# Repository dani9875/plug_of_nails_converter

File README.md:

# Plug of nails converter

# How to
Coming soon...

## Release notes

### Version: v3.0
Changelog:
- USB and free-lead power input  
- J-Link EDU Mini support header

### Version: v2.0
Changelog:
- Component library added as submodule
- KiBot config first usable file finished
. Connectors changed sides

### Version: v1.0
Changelog:
- Initial 2.54 mm and IDC 2x5 header connection

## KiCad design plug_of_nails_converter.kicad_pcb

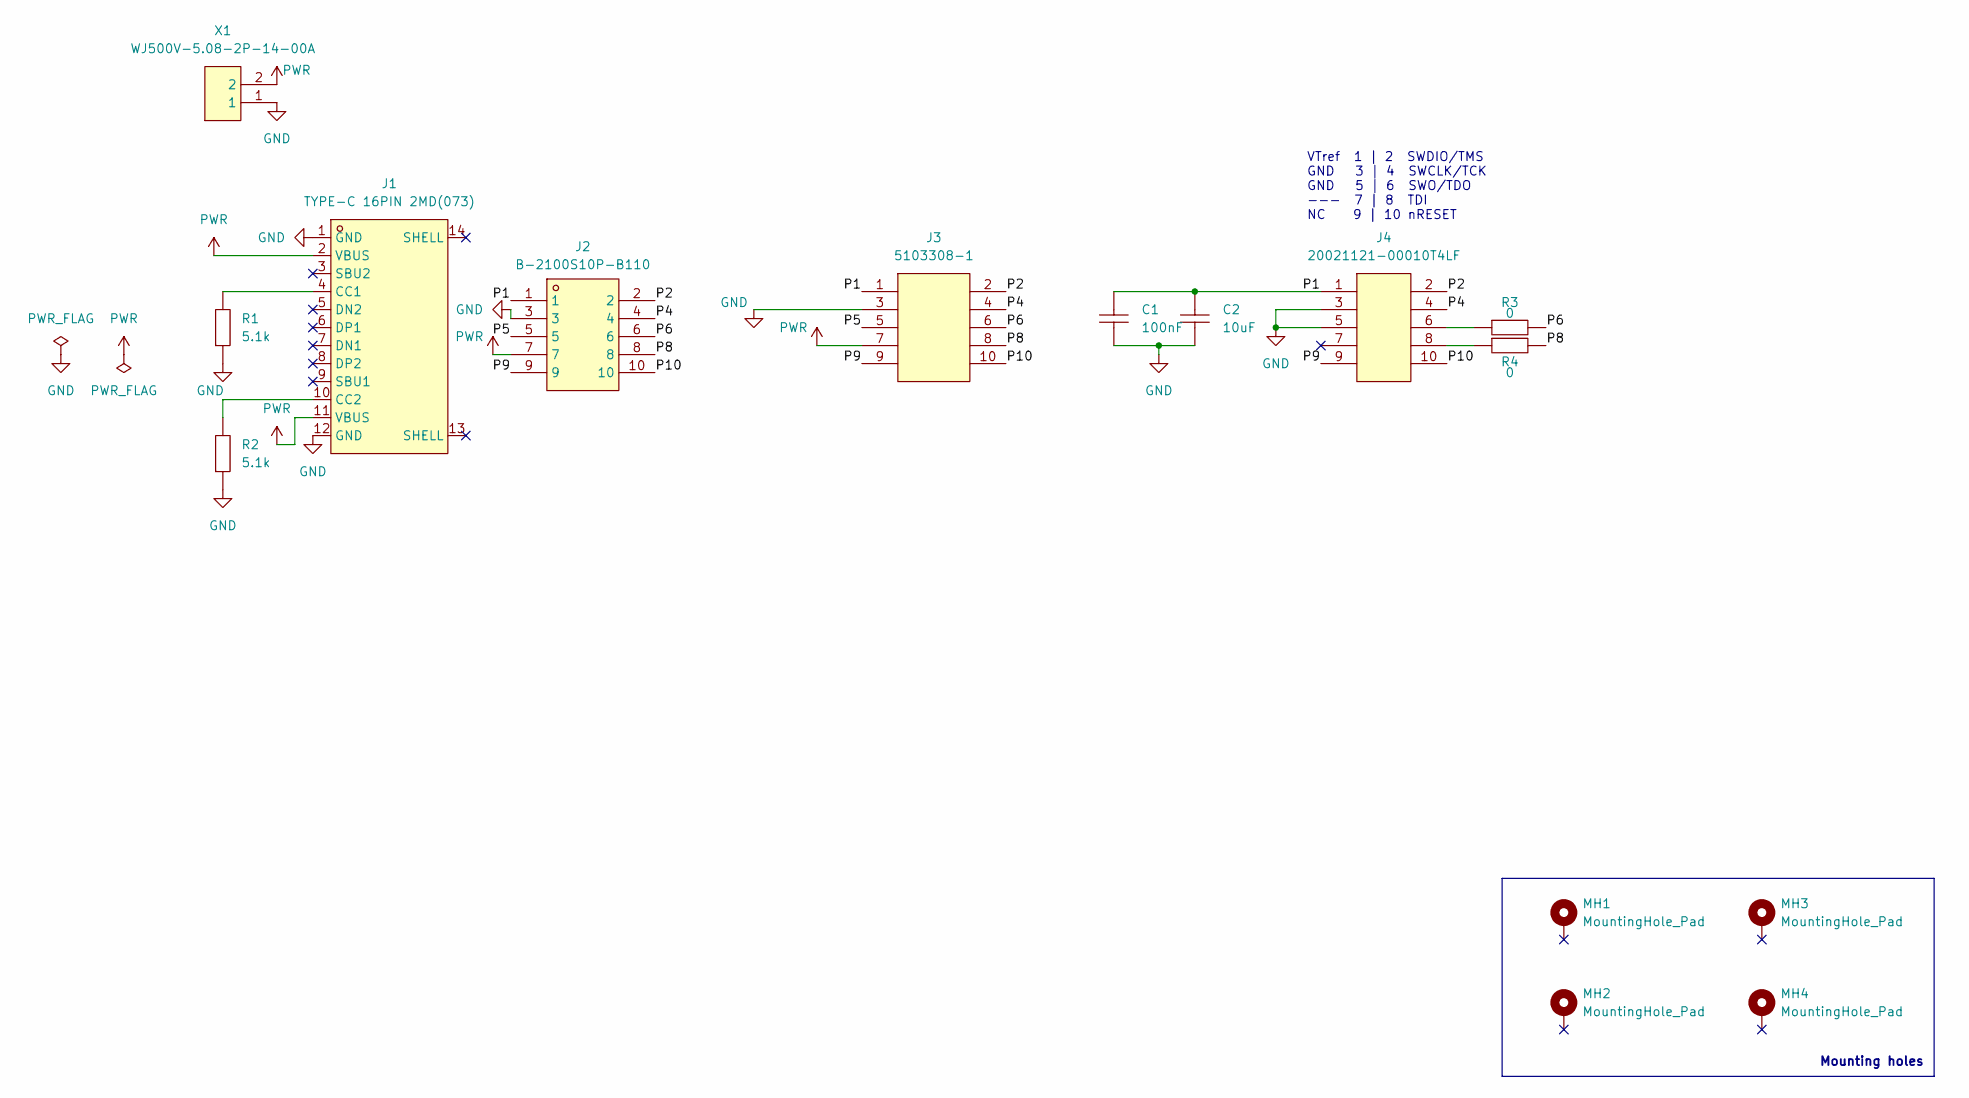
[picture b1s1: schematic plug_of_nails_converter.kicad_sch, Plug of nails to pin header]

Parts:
C1: CC0805KRX7R9BB104; [CAP_SMD_0805_2012Metric]; LCSC Part C49678
C2: CL21A106KOQNNNE; [CAP_SMD_0805_2012Metric]; LCSC Part C1713
J1: TYPE-C 16PIN 2MD(073); [USB_C_16P_RA_FEMALE]SHOU HAN TYPE-C 16PIN 2MD(073); LCSC Part C2765186
J2: B-2100S10P-B110; [10P_HEADER_STR]Ckmtw(Shenzhen Cankemeng) B-2100S10P-B110; LCSC Part C124387
J3: 5103308-1; [10P_2X5_IDC_MALE]TE Connectivity 5103308-1; LCSC Part C86466
J4: 20021121-00010T4LF; [10P_2X5_IDC_1_27MM_MALE]Amphenol ICC 20021121-00010T4LF; LCSC Part C598540
MH1, MH2, MH3, MH4: MountingHole_Pad; [MOUNTING_HOLE]MountingHole_2.2mm_M2_DIN965_Pad
R1, R2: 0805W8F5101T5E; [RES_SMD_0805_2012Metric]; LCSC Part C27834
R3, R4: 0805W8F0000T5E; [RES_SMD_0805_2012Metric]; LCSC Part C17673
X1: WJ500V-5.08-2P-14-00A; [1x2_SCREW_TERMINAL_BLOCK]Ningbo Kangnex Elec WJ500V-5.08-2P; LCSC Part C8465

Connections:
/P1: C1.2, C2.2, J2.1, J3.1, J4.1
/P2: J2.2, J3.2, J4.2
/P4: J2.4, J3.4, J4.4
/P5: J2.5, J3.5
/P6: J2.6, J3.6, R3.2
/P8: J2.8, J3.8, R4.2
/P9: J2.9, J3.9, J4.9
/P10: J2.10, J3.10, J4.10
GND: C1.1, C2.1, J1.1 (GND), J1.12 (GND), J2.3, J3.3, J4.3, J4.5, R1.1, R2.1, X1.1
unnamed: J1.4 (CC1), R1.2
unnamed: J1.10 (CC2), R2.2
unnamed: J4.6, R3.1
unnamed: J4.8, R4.1
PWR: J1.2 (VBUS), J1.11 (VBUS), J2.7, J3.7, X1.2

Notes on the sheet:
VTref 1 | 2 SWDIO/TMS GND 3 | 4 SWCLK/TCK GND 5 | 6 SWO/TDO --- 7 | 8 TDI NC 9 | 10 nRESET
Mounting holes

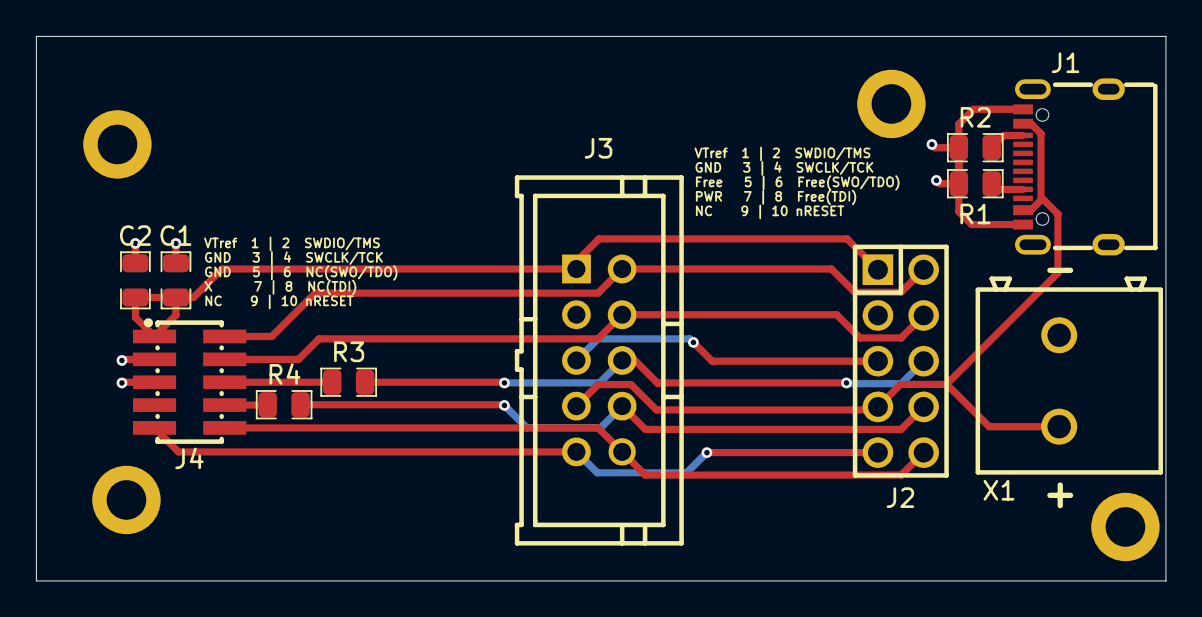
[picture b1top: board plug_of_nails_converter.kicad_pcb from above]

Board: 2 copper layers, 62.8 x 30.2 mm, 15 parts (0 on the bottom side), 14 nets.

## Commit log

2024-07-10 v1 version pushed as initial
2024-07-10 Chaning IDC pin numbers and adding bottom CU layer
2024-07-10 Updating symbols and testing kibot
2024-07-11 Workflow file added
2024-07-11 Installing zip
2024-07-11 Generating release
2024-07-11 Changing from v1 to v2 (release)
2024-07-11 Adding github token
2024-07-12 Component library added as submodule
2024-07-12 Eliminating converter from bom and cpl files and README change
2024-07-16 Fix typo
2024-12-16 Version v3.0 with JLink Edu support
2024-12-16 Updating to upload artifact v4
